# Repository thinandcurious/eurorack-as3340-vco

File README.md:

# eurorack-as3340-vco

Design based on Skull & Circuits VCO-1: https://www.skullandcircuits.com/the-oscillator-one

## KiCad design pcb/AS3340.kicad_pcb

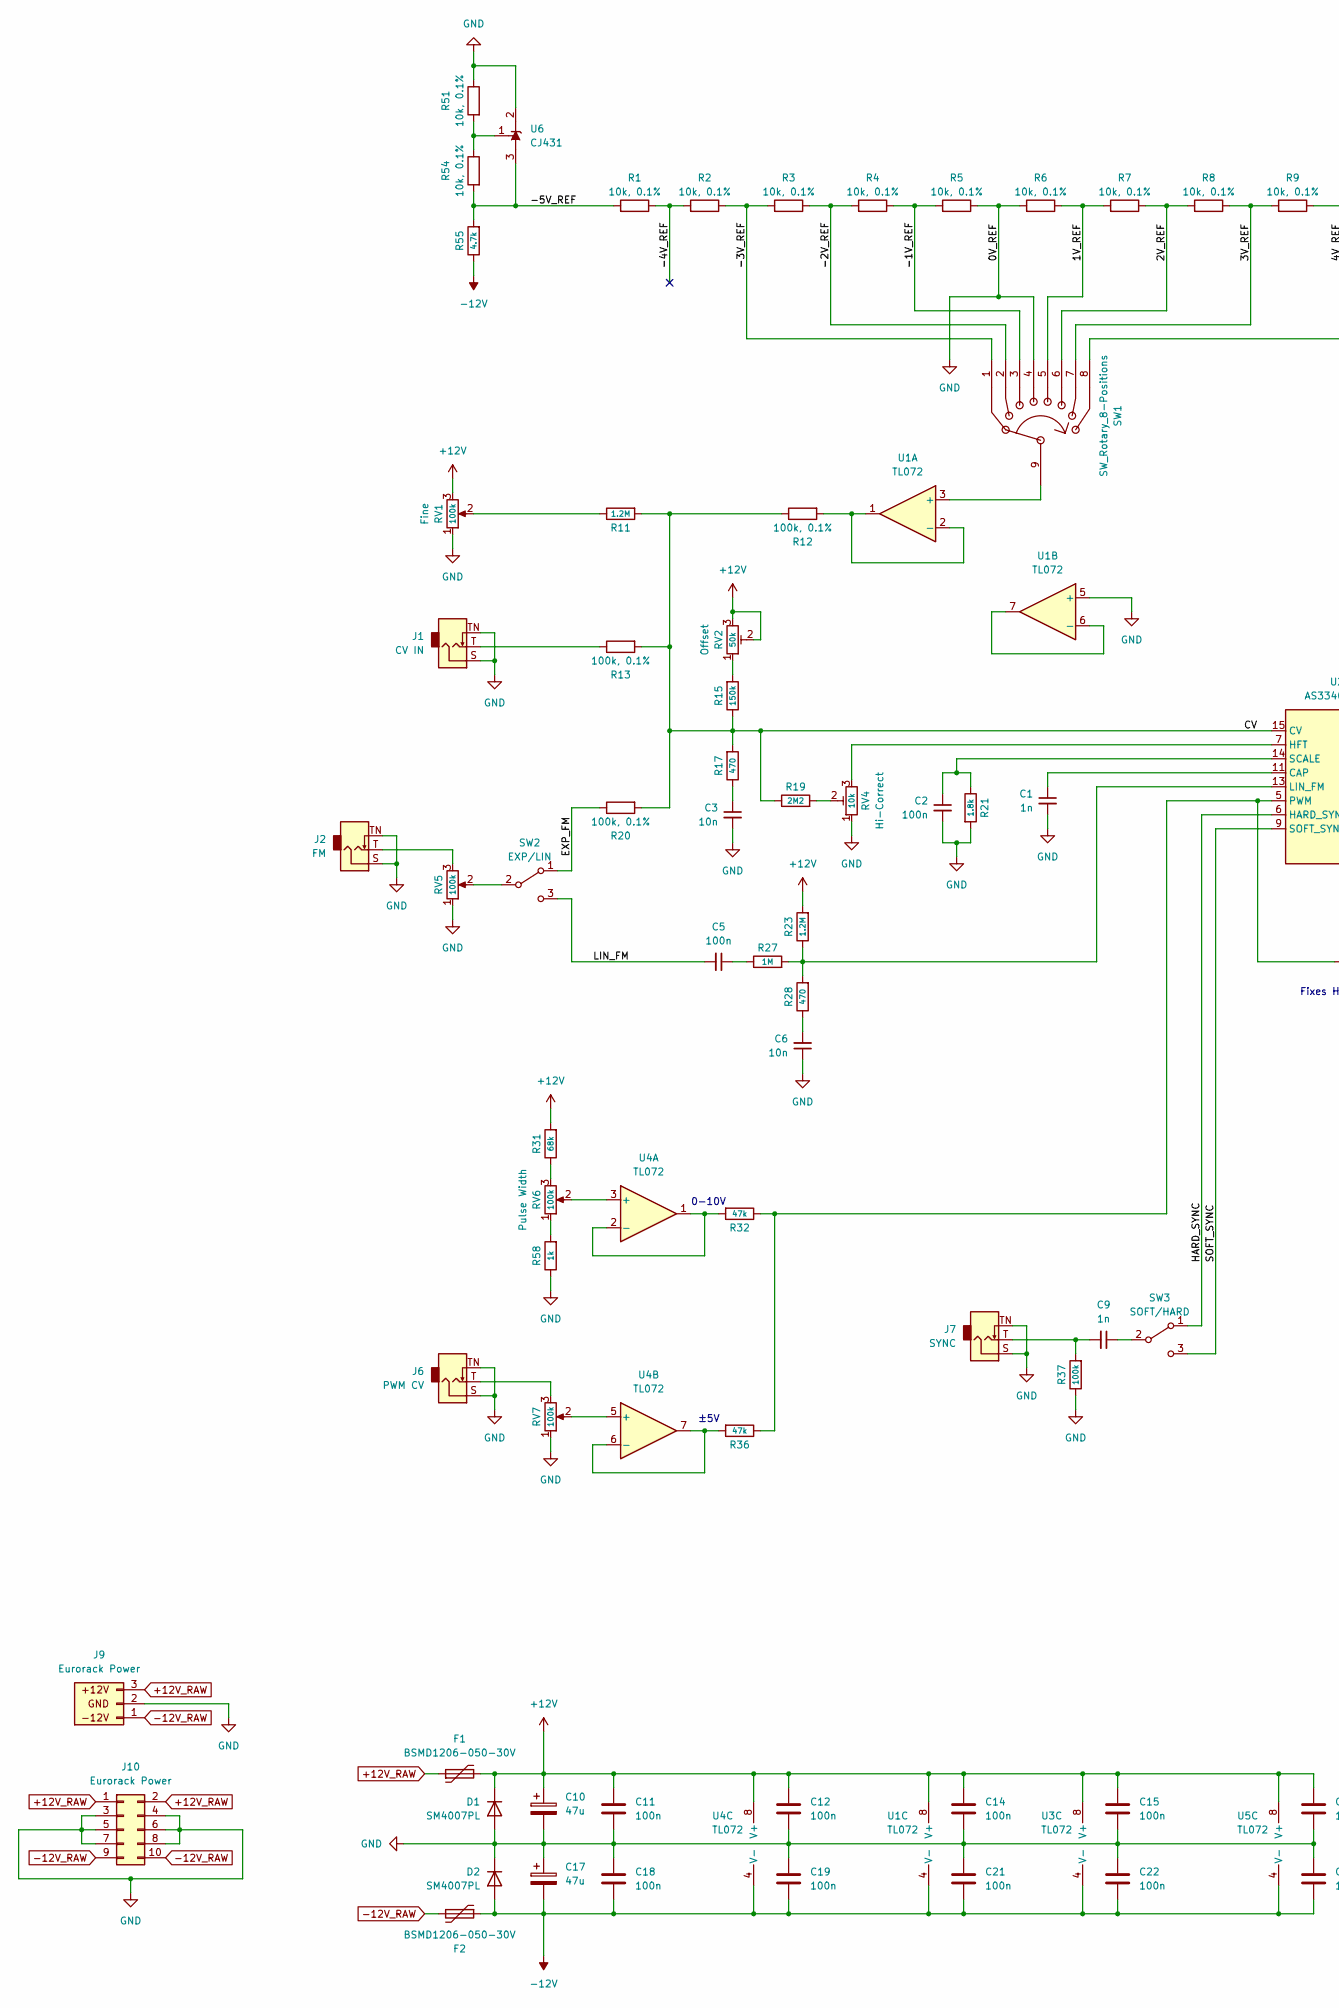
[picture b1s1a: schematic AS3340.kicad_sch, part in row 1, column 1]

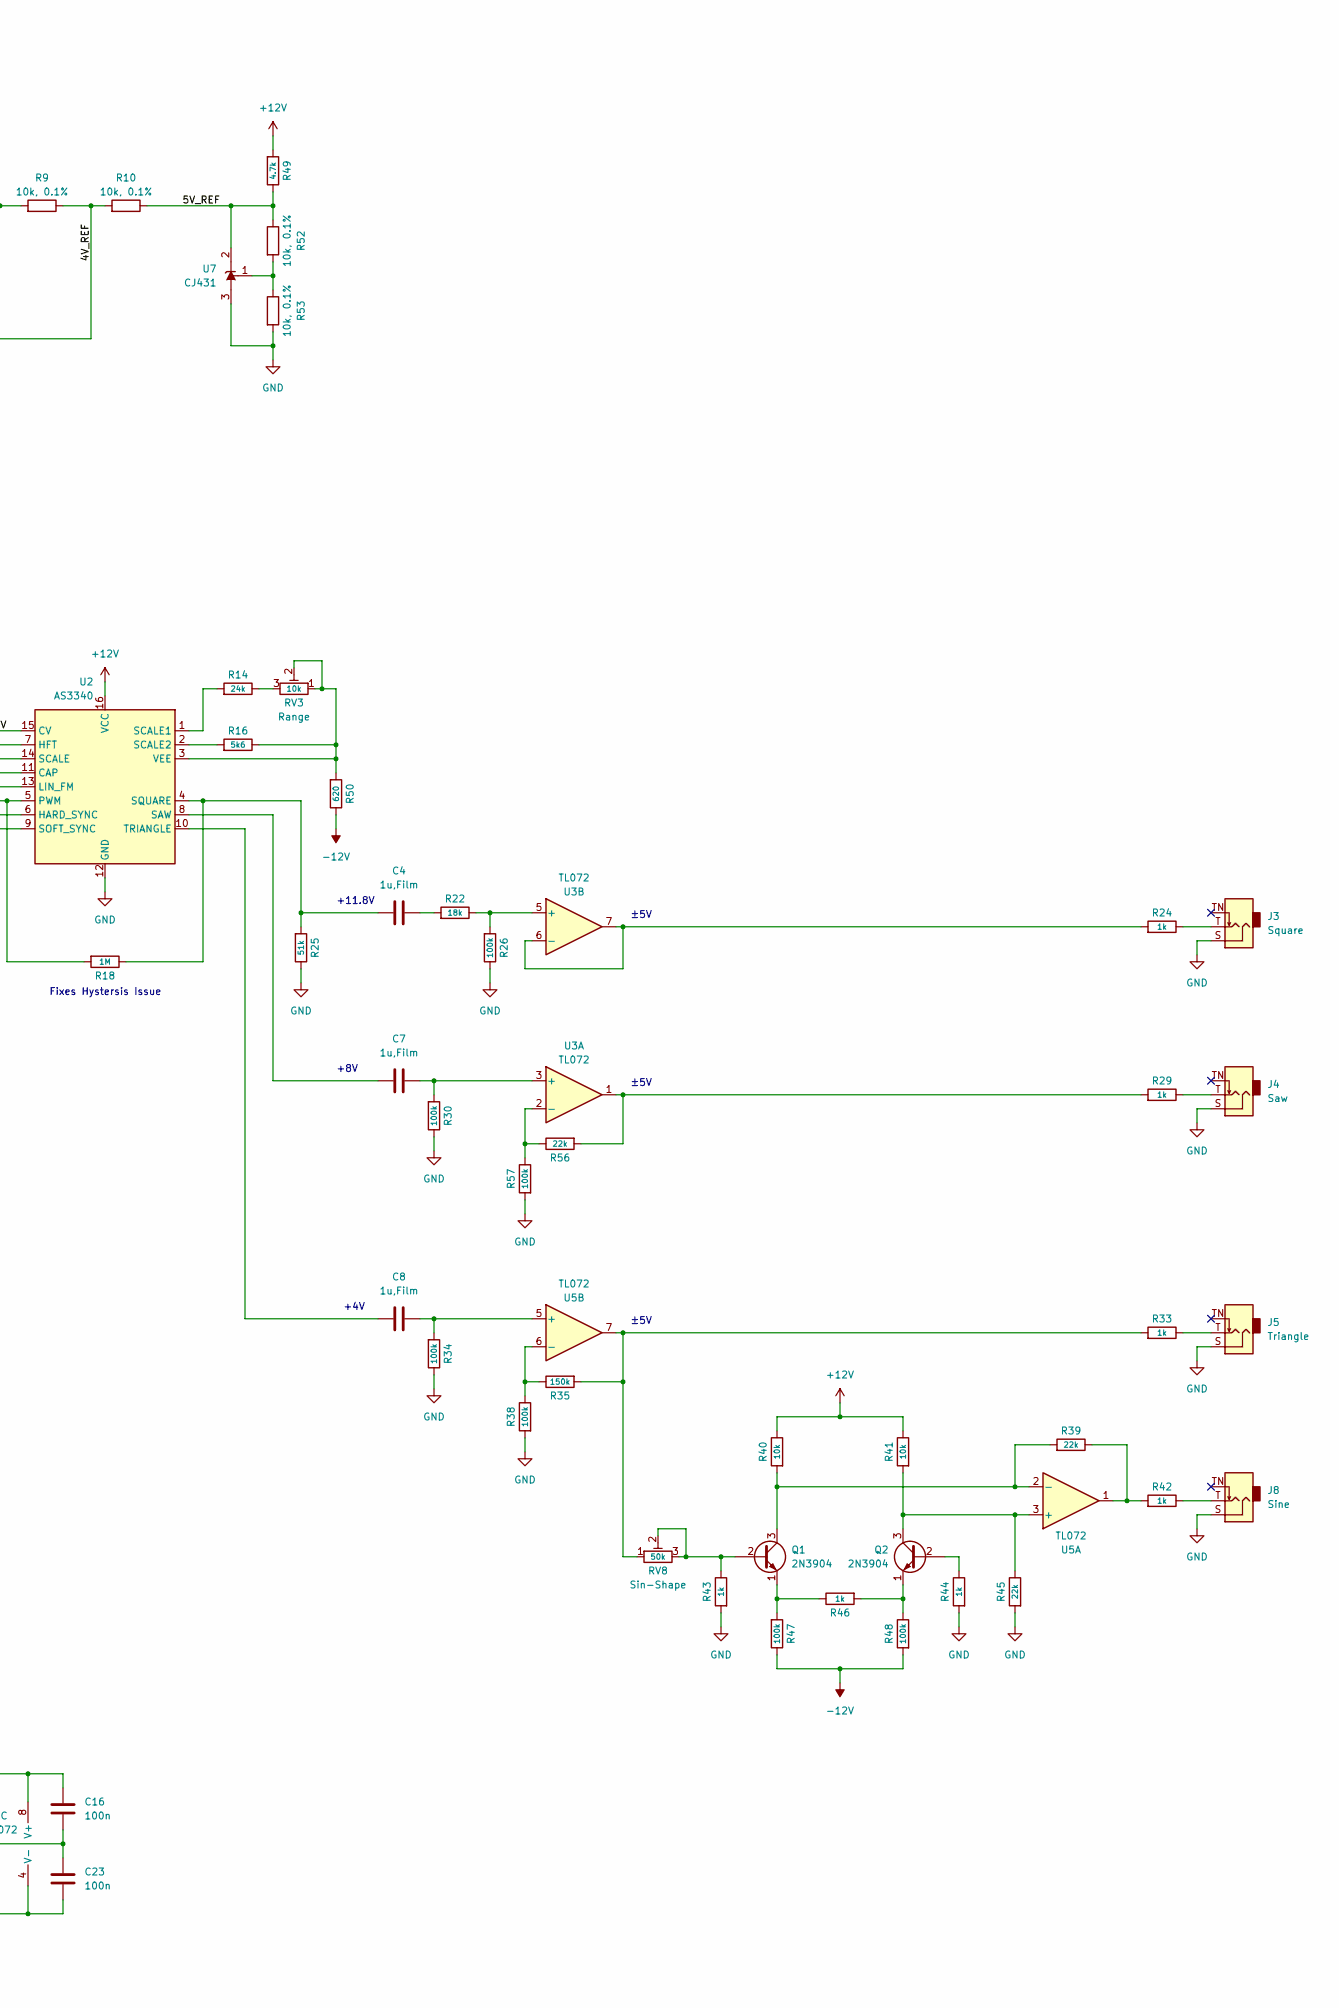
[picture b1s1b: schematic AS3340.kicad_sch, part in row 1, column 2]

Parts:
C1, C9: 1n; C_0603_1608Metric; LCSC C1588
C2, C5, C11, C12, C14, C15, C16, C18, C19, C21, C22, C23: 100n; C_0603_1608Metric; LCSC C14663
C3, C6: 10n; C_0603_1608Metric; LCSC C57112
C4, C7, C8: 1u,Film; C_Rect_L7.2mm_W5.5mm_P5.00mm_FKS2_FKP2_MKS2_MKP2
C10, C17: 47u; CP_Radial_D6.3mm_P2.50mm
D1, D2: SM4007PL; D_SOD-123F; LCSC C64898
F1, F2: BSMD1206-050-30V; Fuse_1206_3216Metric; LCSC C883126
J1: CV IN; Jack_3.5mm_PJ398SM_Vertical
J2: FM; Jack_3.5mm_PJ398SM_Vertical
J3: Square; Jack_3.5mm_PJ398SM_Vertical
J4: Saw; Jack_3.5mm_PJ398SM_Vertical
J5: Triangle; Jack_3.5mm_PJ398SM_Vertical
J6: PWM CV; Jack_3.5mm_PJ398SM_Vertical
J7: SYNC; Jack_3.5mm_PJ398SM_Vertical
J8: Sine; Jack_3.5mm_PJ398SM_Vertical
J9: Eurorack Power; JST_XH_B3B-XH-A_1x03_P2.50mm_Vertical
J10: Eurorack Power; PinHeader_2x05_P2.54mm_Vertical
Q1, Q2: 2N3904; TO-92_Inline_Wide
R1, R2, R3, R4, R5, R6, R7, R8, R9, R10, R51, R52, R53, R54: 10k, 0.1%; R_0603_1608Metric; LCSC C309083
R11: 1.2M; R_1206_3216Metric_Pad1.30x1.75mm_HandSolder; LCSC C22107
R12, R13, R20: 100k, 0.1%; R_0603_1608Metric; LCSC C335088
R14: 24k; R_0603_1608Metric; LCSC C23352
R15, R35: 150k; R_0603_1608Metric; LCSC C22807
R16: 5k6; R_0603_1608Metric; LCSC C23189
R17, R28: 470; R_0603_1608Metric; LCSC C23179
R18, R27: 1M; R_0603_1608Metric; LCSC C22935
R19: 2M2; R_0603_1608Metric; LCSC C22938
R21: 1.8k; R_0603_1608Metric; LCSC C4177
R22: 18k; R_0603_1608Metric; LCSC C25810
R23: 1.2M; R_1206_3216Metric; LCSC C22107
R24, R29, R33, R42, R43, R44, R46, R58: 1k; R_0603_1608Metric; LCSC C21190
R25: 51k; R_0603_1608Metric; LCSC C23196
R26, R30, R34, R37, R38, R47, R48, R57: 100k; R_0603_1608Metric; LCSC C25803
R31: 68k; R_0603_1608Metric; LCSC C23231
R32, R36: 47k; R_0603_1608Metric; LCSC C25819
R39, R45, R56: 22k; R_0603_1608Metric; LCSC C31850
R40, R41: 10k; R_0603_1608Metric; LCSC C25804
R49, R55: 4.7k; R_0603_1608Metric; LCSC C23162
R50: 620; R_0603_1608Metric; LCSC C23220
RV1, RV5, RV6, RV7: 100k; Potentiometer_Alpha_RD901F
RV2, RV8: 50k; Potentiometer_Bourns_3296Y_Vertical
RV3, RV4: 10k; Potentiometer_Bourns_3296Y_Vertical
SW1: SW_Rotary_8-Positions; Switch_1P8T_Rotary
SW2: EXP/LIN; Switch_SPDT_Micro-Toggle
SW3: SOFT/HARD; Switch_SPDT_Micro-Toggle
U1, U3, U4, U5: TL072; SOIC-8_3.9x4.9mm_P1.27mm; LCSC C6961
U2: AS3340; DIP-16_W7.62mm
U6, U7: CJ431; SOT-23; LCSC C3113

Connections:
+12V: C10.1, C11.1, C12.1, C14.1, C15.1, C16.1, D1.1 (K), F1.2, R23.2, R31.2, R40.1, R41.1, R49.2, RV1.3, RV2.2, RV2.3, U1.8 (V+), U2.16 (VCC), U3.8 (V+), U4.8 (V+), U5.8 (V+)
+12V_RAW: F1.1, J9.3, J10.1, J10.2
-12V: C17.2, C18.2, C19.2, C21.2, C22.2, C23.2, D2.2 (A), F2.1, R47.1, R48.2, R50.1, R55.1, U1.4 (V-), U3.4 (V-), U4.4 (V-), U5.4 (V-)
-12V_RAW: F2.2, J9.1, J10.9, J10.10
/1V_REF: R6.1, R7.2, SW1.5
/2V_REF: R7.1, R8.2, SW1.6
/3V_REF: R8.1, R9.2, SW1.7
/4V_REF: R9.1, R10.2, SW1.8
/5V_REF: R10.1, R49.1, R52.1, U7.2 (K)
/-1V_REF: R4.1, R5.2, SW1.3
/-2V_REF: R3.1, R4.2, SW1.2
/-3V_REF: R2.1, R3.2, SW1.1
/-4V_REF: R1.1, R2.2
/-5V_REF: R1.2, R54.2, R55.2, U6.3 (A)
/CV: R11.2, R12.1, R13.2, R15.1, R17.2, R19.1, R20.2, U2.15 (CV)
/EXP_FM: R20.1, SW2.1 (A)
/HARD_SYNC: SW3.1 (A), U2.6 (HARD_SYNC)
/LIN_FM: C5.2, SW2.3 (C)
/SOFT_SYNC: SW3.3 (C), U2.9 (SOFT_SYNC)
GND: C1.2, C2.2, C3.2, C6.1, C10.2, C11.2, C12.2, C14.2, C15.2, C16.2, C17.1, C18.1, C19.1, C21.1, C22.1, C23.1, D1.2 (A), D2.1 (K), J1.S, J1.TN, J2.S, J2.TN, J3.S, J4.S, J5.S, J6.S, J6.TN, J7.S, J7.TN, J8.S, J9.2, J10.3, J10.4, J10.5, J10.6, J10.7, J10.8, R5.1, R6.2, R21.2, R25.1, R26.1, R30.1, R34.1, R37.1, R38.2, R43.2, R44.2, R45.2, R51.1, R53.2, R57.2, R58.1, RV1.1, RV4.1, RV5.1, RV7.1, SW1.4, U1.5 (+), U2.12 (GND), U6.2 (K), U7.3 (A)
unnamed: C1.1, U2.11 (CAP)
unnamed: C2.1, R21.1, U2.14 (SCALE)
unnamed: C3.1, R17.1
unnamed: C4.1, R18.1, R25.2, U2.4 (SQUARE)
unnamed: C4.2, R22.2
unnamed: C5.1, R27.1
unnamed: C6.2, R28.1
unnamed: C7.1, U2.8 (SAW)
unnamed: C7.2, R30.2, U3.3 (+)
unnamed: C8.1, U2.10 (TRIANGLE)
unnamed: C8.2, R34.2, U5.5 (+)
unnamed: C9.1, SW3.2 (B)
unnamed: C9.2, J7.T, R37.2
unnamed: J1.T, R13.1
unnamed: J2.T, RV5.3
unnamed: J3.T, R24.1
unnamed: J4.T, R29.1
unnamed: J5.T, R33.1
unnamed: J6.T, RV7.3
unnamed: J8.T, R42.1
unnamed: Q1.1 (E), R46.1, R47.2
unnamed: Q1.2 (B), R43.1, RV8.2, RV8.3
unnamed: Q1.3 (C), R39.2, R40.2, U5.2 (-)
unnamed: Q2.1 (E), R46.2, R48.1
unnamed: Q2.2 (B), R44.1
unnamed: Q2.3 (C), R41.2, R45.1, U5.3 (+)
unnamed: R11.1, RV1.2
unnamed: R12.2, U1.1, U1.2 (-)
unnamed: R14.1, RV3.3
unnamed: R14.2, U2.1 (SCALE1)
unnamed: R15.2, RV2.1
unnamed: R16.1, R50.2, RV3.1, RV3.2, U2.3 (VEE)
unnamed: R16.2, U2.2 (SCALE2)
unnamed: R18.2, R32.1, R36.1, U2.5 (PWM)
unnamed: R19.2, RV4.2
unnamed: R22.1, R26.2, U3.5 (+)
unnamed: R23.1, R27.2, R28.2, U2.13 (LIN_FM)
unnamed: R24.2, U3.6 (-), U3.7
unnamed: R29.2, R56.2, U3.1
unnamed: R31.1, RV6.3
unnamed: R32.2, U4.1, U4.2 (-)
unnamed: R33.2, R35.2, RV8.1, U5.7
unnamed: R35.1, R38.1, U5.6 (-)
unnamed: R36.2, U4.6 (-), U4.7
unnamed: R39.1, R42.2, U5.1
unnamed: R51.2, R54.1, U6.1 (REF)
unnamed: R52.2, R53.1, U7.1 (REF)
unnamed: R56.1, R57.1, U3.2 (-)
unnamed: R58.2, RV6.1
unnamed: RV4.3, U2.7 (HFT)
unnamed: RV5.2, SW2.2 (B)
unnamed: RV6.2, U4.3 (+)
unnamed: RV7.2, U4.5 (+)
unnamed: SW1.9, U1.3 (+)
unnamed: U1.6 (-), U1.7

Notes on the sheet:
±5V
Fixes Hystersis Issue
0-10V
+8V
+11.8V
+4V

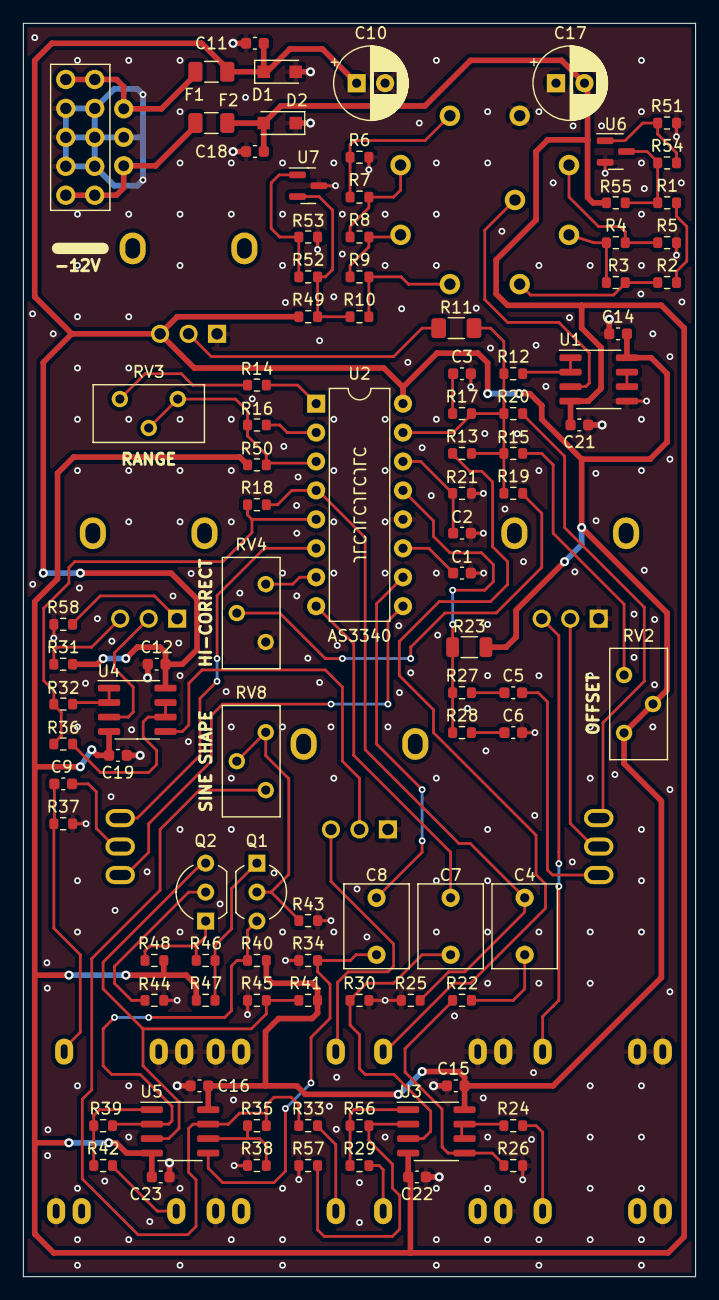
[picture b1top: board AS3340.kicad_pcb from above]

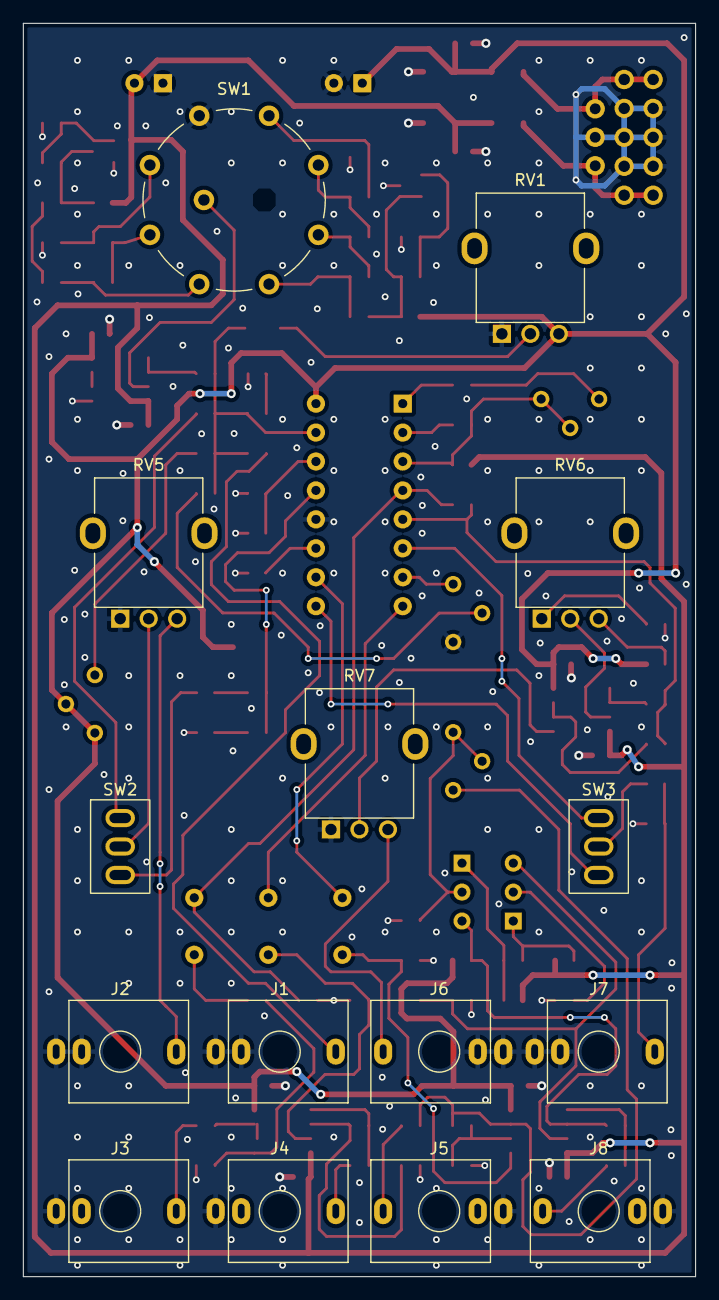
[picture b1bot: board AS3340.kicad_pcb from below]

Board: 2 copper layers, 59.0 x 110.0 mm, 113 parts (15 on the bottom side), 75 nets.

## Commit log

2025-03-17 upload
